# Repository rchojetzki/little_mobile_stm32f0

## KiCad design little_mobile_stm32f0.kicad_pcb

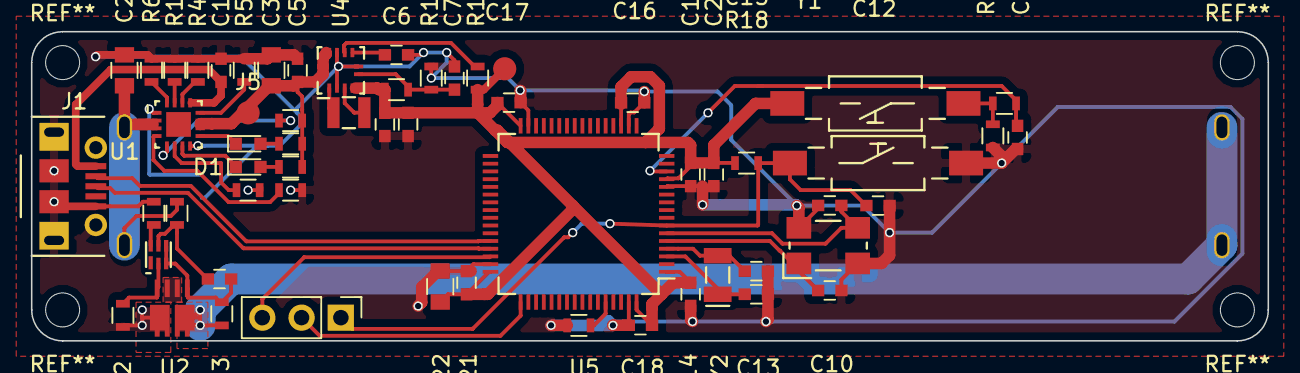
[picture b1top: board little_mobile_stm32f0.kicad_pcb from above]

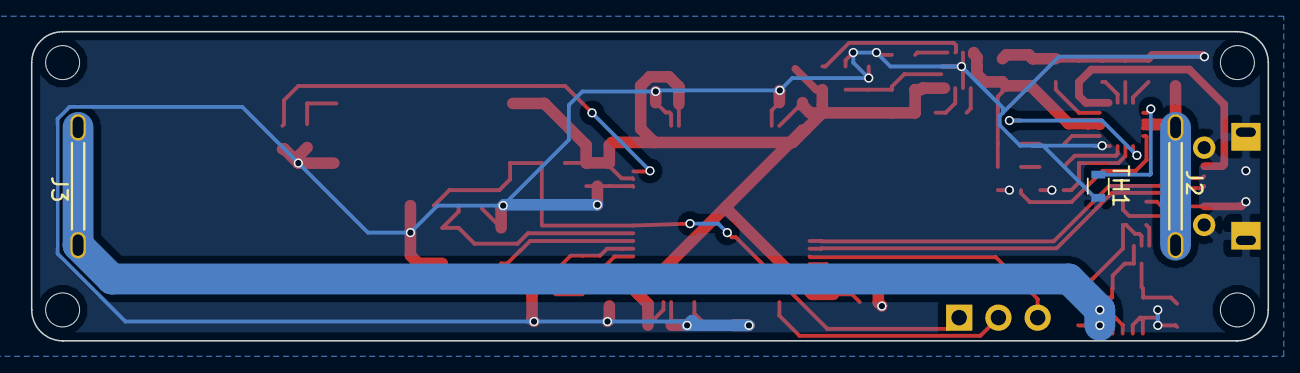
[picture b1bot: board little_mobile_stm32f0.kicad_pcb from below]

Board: 2 copper layers, 80.0 x 20.0 mm, 62 parts (3 on the bottom side), 40 nets.

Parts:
C1, C20: 1u; C_0603
C2, C3, C22: 4.7u; C_0805
C4, C12, C14, C16, C17, C18, C21, C23: 100n; C_0603
C5, C8, C9: 10u; C_0603
C6: 4.7n; C_0603
C7: 10p; C_0603
C10, C11: 40p; C_0603
C13, C15: 25p; C_0603
C19: 10n; C_0603
D1, D2: LED; LED_0603
J1: USB_OTG; Molex_1050170001_MicroUSB_B
J2: BAT+ Contact; KEYSTONE_109-2_Battery_Contact
J3: BAT- Contact; KEYSTONE_109-2_Battery_Contact
J4: Header_SWD; Pin_Header_Straight_1x03_Pitch2.54mm
J5: TEST_POWER_RAW; Measurement_Point_Round-SMD-Pad_Small
J6: TEST_3v3; Measurement_Point_Round-SMD-Pad_Small
L1: 1.5u; Murata-DFE252010C-Series
R1: 2.2k; R_0603
R2, R3: 5.1M; R_0603
R4: 46.4k; R_0603
R5: 1.03k; R_0603
R6: 742; R_0603
R7, R10: 1.5k; R_0603
R8: 4.7; R_0603
R9, R11, R12, R18, R19, R20: 10k; R_0603
R13: 330; R_0603
R14: 562k; R_0603
R15: 100k; R_0603
R16: 180; R_0603
R17: 510; R_0603
SW1, SW2: SW_DIP_x01; FSMSM_TE_Switch
TH1: Thermistor_NTC; R_0603
U1: bq24073
U2: CSD87313DMS; csd87313DMS
U3: bq29732; WSON_bq2973
U4: TPS63050RMW; VQFN_tps6350
U5: STM32F072RBTx; LQFP-64_10x10mm_Pitch0.5mm
Y1: 8MHz; LFXTAL069277Reel_Crystal_8MHz
Y2: 32.768k; CM7V-T1A_32.768kHz_Crystal

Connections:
/little_mobile_stm32f0_micro/NRST: C12.2, J4.1, R18.2, SW1.2, U5.7
/little_mobile_stm32f0_micro/SWD_CLK: J4.2, U5.49
/little_mobile_stm32f0_micro/SWD_IO: J4.3, U5.46
/little_mobile_stm32f0_micro/USB_D+: J1.3, U5.45
/little_mobile_stm32f0_micro/USB_D-: J1.2, U5.44
/little_mobile_stm32f0_power/3v3: C8.1, C9.1, C14.1, C16.2, C17.2, C18.2, C19.2, C20.2, C21.2, C22.2, J6.1, R14.1, R15.2, R18.1, SW2.1, U4.4, U5.1, U5.13, U5.19, U5.32, U5.48, U5.64
/little_mobile_stm32f0_power/BAT+: C2.1, J2.1, J2.2, R13.1, U1.2, U1.3
/little_mobile_stm32f0_power/BAT-: J3.1, J3.2, R3.1, U2.7, U2.8
/little_mobile_stm32f0_power/BAT_TERMAL_SENSE: TH1.1, U1.1
/little_mobile_stm32f0_power/CE: R9.1, U1.4
/little_mobile_stm32f0_power/EN1: R12.1, U1.6
/little_mobile_stm32f0_power/EN2: R8.2, U1.5
/little_mobile_stm32f0_power/POWER_RAW: C3.2, C5.1, J5.1, R7.2, R8.1, R10.2, U1.10, U1.11, U4.10, U4.11, U4.12
/little_mobile_stm32f0_power/TD: R11.1, U1.15
/little_mobile_stm32f0_power/USB_5V: C1.1, J1.1, U1.13
GND: C1.2, C2.2, C3.1, C5.2, C6.2, C7.1, C8.2, C9.2, C10.2, C11.2, C12.1, C13.2, C14.2, C15.2, C16.1, C17.1, C18.1, C19.1, C20.1, C21.1, C22.1, C23.2, J1.5, J1.6, R1.1, R2.1, R4.2, R5.2, R6.2, R9.2, R11.2, R12.2, R16.2, R17.2, R20.2, SW1.1, TH1.2, U1.8, U2.5, U2.6, U4.2, U4.6, U4.9, U5.12, U5.18, U5.31, U5.47, U5.63, Y1.2, Y1.4
unnamed: C4.1, R13.2, U3.5
unnamed: C4.2, R3.2, U2.1, U3.3, U3.4
unnamed: C6.1, U4.7
unnamed: C7.2, R14.2, R16.1, U4.5
unnamed: C10.1, U5.5, Y1.1
unnamed: C11.1, U5.6, Y1.3
unnamed: C13.1, U5.3, Y2.1
unnamed: C15.1, U5.4, Y2.2
unnamed: C23.1, R19.1, U5.14
unnamed: D1.1, U1.7
unnamed: D1.2, R7.1
unnamed: D2.1, U1.9
unnamed: D2.2, R10.1
unnamed: L1.1, U4.3
unnamed: L1.2, U4.1
unnamed: R1.2, U3.6
unnamed: R2.2, U2.4, U3.2
unnamed: R4.1, U1.14
unnamed: R5.1, U1.12
unnamed: R6.1, U1.16
unnamed: R15.1, U4.8
unnamed: R17.1, U5.60
unnamed: R19.2, R20.1, SW2.2
unnamed: U2.2, U2.3

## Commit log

2018-02-10 :circus_tent: Added .gitattributes & .gitignore files
2018-08-18 initial setup complete using TI Parts for power 3v3 Regulated output by Buck/Boost converter, efficiency 85% to 91% board will by only solderable in oven TODO: battery protection not calculated TODO: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
2018-08-19 pcb Layout nearly completed
2018-08-19 board would be ready for production
2018-08-20 deleted stm32f0-disco zips
